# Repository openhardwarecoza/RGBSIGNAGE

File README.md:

# RGBSIGNAGE
Electronics and Firmware for an ESP8266 based RGB Sign

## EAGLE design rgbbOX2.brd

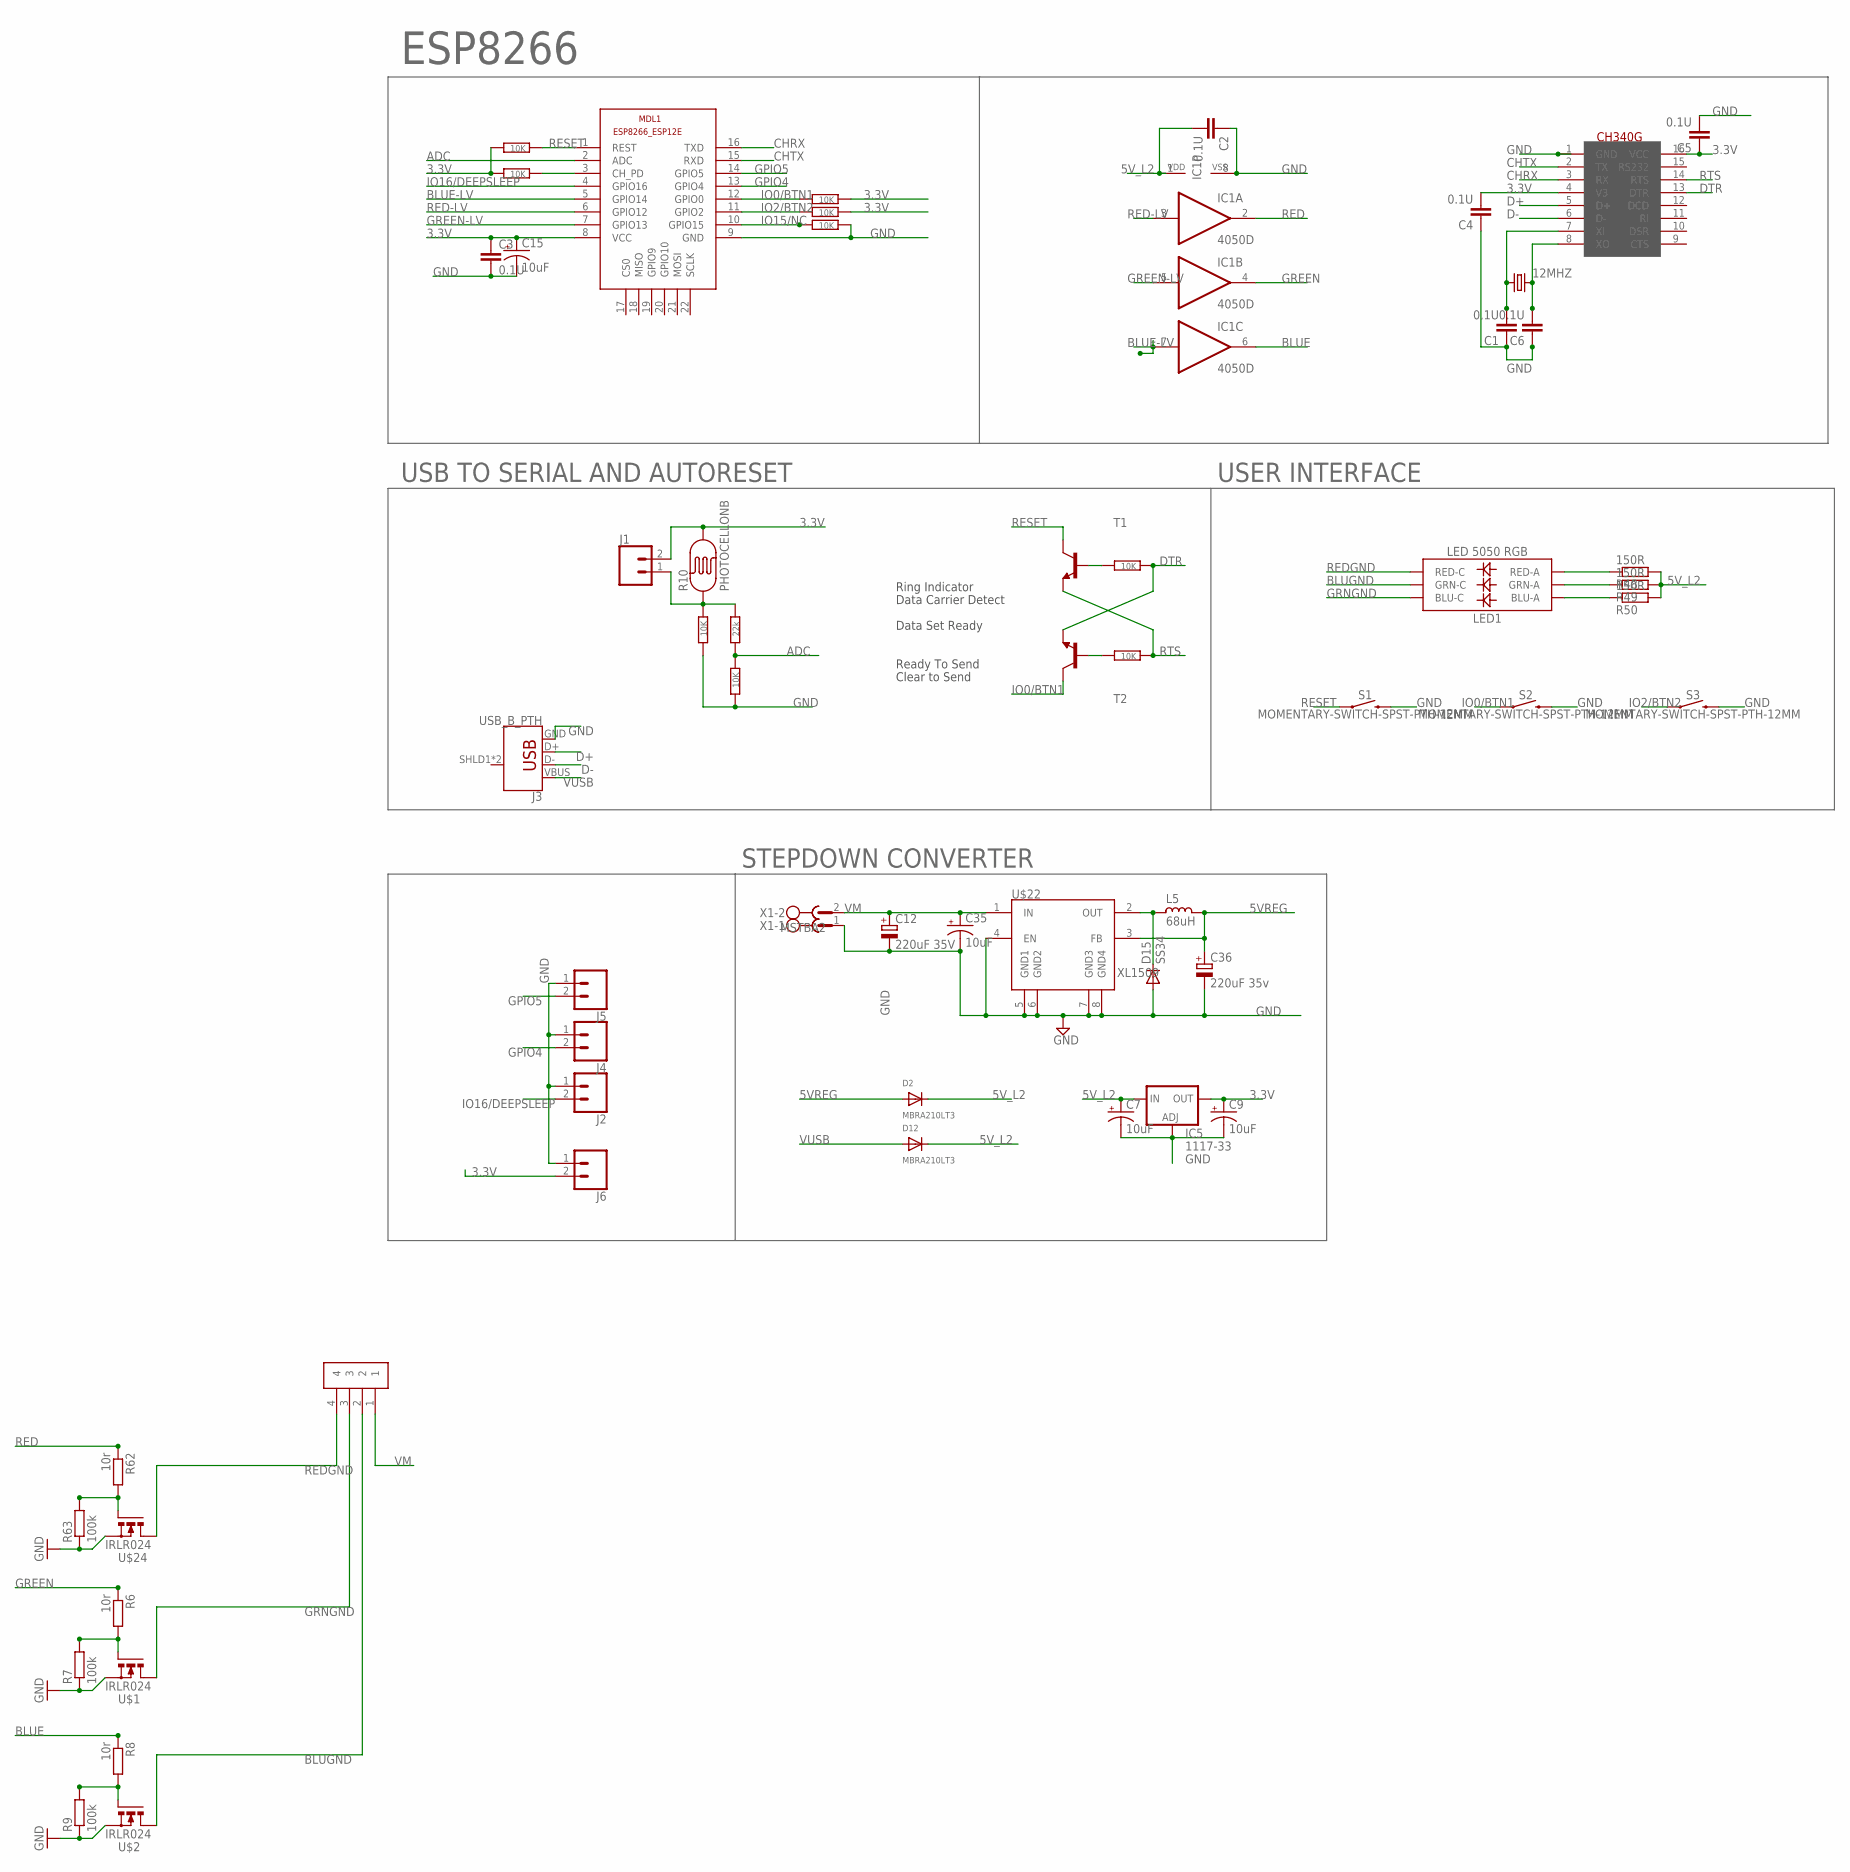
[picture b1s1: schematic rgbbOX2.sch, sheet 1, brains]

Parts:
12MHZ: CRYSTALHC49UP; HC49UP
C1, C2, C3, C4, C5, C6: 0.1U; C1206
C7, C9, C15, C35: 10uF; EIA3216
C12: 220uF 35V; E3,5-8
C36: 220uF 35v; E3,5-8
CON25: Phoenix Pluggable 3.81mm 4 way; 3.81MM-4WAY-PLUGGABLE-SCREW
D2, D12: MBRA210LT3; SMADIODE
D15: SS34; DO-214AC
IC1: 4050D; SO16
IC5: 1117-33; SOT223
J1, J2, J4, J5, J6: CONN_02LOCK; 1X02_LOCK
J3: USB_B_PTH; USB-B-PTH
L5: 68uH; CD75
LED1: LED 5050 RGB; LED-TRICOLOR-5050
MDL1: ESP8266-12EESP8266-ESP12E; ESP8266-ESP12E
R1, R2, R4, R5, R11, R12, R28, R29, R31: 10K; R1206
R3: 22k; R1206
R6, R8, R62: 10r; R1206
R7, R9, R63: 100k; R1206
R10: PHOTOCELLONB; ON_BOARD
R48, R49, R50: 150R; R1210
S1, S2, S3: MOMENTARY-SWITCH-SPST-PTH-12MM; TACTILE_SWITCH_PTH_12MM
T1, T2: MMBT2222ALT1-NPN-SOT23-BEC; SOT23-BEC
U$1, U$2, U$24: IRLR024; D-PAK_TO252AA
U$4: CH340G; SOIC16
U$22: XL1509; SO08
X1: MSTBA2

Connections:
3.3V: C3.1, C4.2, C5.1, C9.A (+), C15.A (+), IC5.4 (OUT), J1.2, J6.2, MDL1.8 (VCC), R10.2, R11.2, R12.2, R28.1, R29.1, U$4.4 (V3), U$4.16 (VCC)
5VREG: C36.+, D2.A, L5.1, U$22.3 (FB)
5V_L2: C2.2, C7.A (+), D2.C, D12.C, IC1.1 (VDD), IC5.3 (IN), R48.2, R49.2, R50.2
ADC: MDL1.2 (ADC), R3.1, R4.2
BLUE: IC1.6 (O), R8.1
BLUE-LV: IC1.7 (I), MDL1.5 (GPIO14)
BLUGND: CON25.2, LED1.6 (GRN-C), U$2.4 (D)
CHRX: MDL1.16 (TXD), U$4.3 (RX)
CHTX: MDL1.15 (RXD), U$4.2 (TX)
D+: J3.D+, U$4.5 (D+)
D-: J3.D-, U$4.6 (D-)
DTR: R1.2, T2.E, U$4.13 (DTR)
GND: C1.1, C2.1, C3.2, C4.1, C5.2, C6.1, C7.C (-), C9.C (-), C12.-, C15.C (-), C35.C (-), C36.-, D15.2 (A), IC1.8 (VSS), IC5.1 (ADJ), J2.1, J3.GND, J4.1, J5.1, J6.1, MDL1.9 (GND), R4.1, R5.1, R7.1, R9.1, R31.2, R63.1, S1.3 (2), S2.3 (2), S3.3 (2), U$1.3 (S), U$2.3 (S), U$4.1 (GND), U$22.4 (EN), U$22.5 (GND1), U$22.6 (GND2), U$22.7 (GND3), U$22.8 (GND4), U$24.3 (S), X1.1
GPIO4: J4.2, MDL1.13 (GPIO4)
GPIO5: J5.2, MDL1.14 (GPIO5)
GREEN: IC1.4 (O), R6.1
GREEN-LV: IC1.5 (I), MDL1.7 (GPIO13)
GRNGND: CON25.3, LED1.4 (BLU-C), U$1.4 (D)
IO0/BTN1: MDL1.12 (GPIO0), R12.1, S2.1, T2.C
IO2/BTN2: MDL1.11 (GPIO2), R11.1, S3.1
IO15/NC: MDL1.10 (GPIO15), R31.1
IO16/DEEPSLEEP: J2.2, MDL1.4 (GPIO16)
unnamed: R6.2, R7.2, U$1.1 (G)
unnamed: R62.2, R63.2, U$24.1 (G)
unnamed: D15.1 (C), L5.2, U$22.2 (OUT)
unnamed: 12MHZ.1, C1.2, U$4.7 (XI)
unnamed: 12MHZ.2, C6.2, U$4.8 (XO)
unnamed: R8.2, R9.2, U$2.1 (G)
unnamed: R1.1, T1.B
unnamed: R2.1, T2.B
unnamed: J1.1, R3.2, R5.2, R10.1
unnamed: MDL1.3 (CH_PD), R28.2
unnamed: LED1.3 (BLU-A), R50.1
unnamed: LED1.1 (GRN-A), R49.1
unnamed: LED1.2 (RED-A), R48.1
RED: IC1.2 (O), R62.1
RED-LV: IC1.3 (I), MDL1.6 (GPIO12)
REDGND: CON25.4, LED1.5 (RED-C), U$24.4 (D)
RESET: MDL1.1 (REST), R29.2, S1.1, T1.C
RTS: R2.2, T1.E, U$4.14 (RTS)
VM: C12.+, C35.A (+), CON25.1, U$22.1 (IN), X1.2
VUSB: D12.A, J3.VBUS

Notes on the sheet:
USB TO SERIAL AND AUTORESET
ESP8266
USER INTERFACE
Ring Indicator
Data Carrier Detect
Data Set Ready
Ready To Send
Clear to Send
STEPDOWN CONVERTER

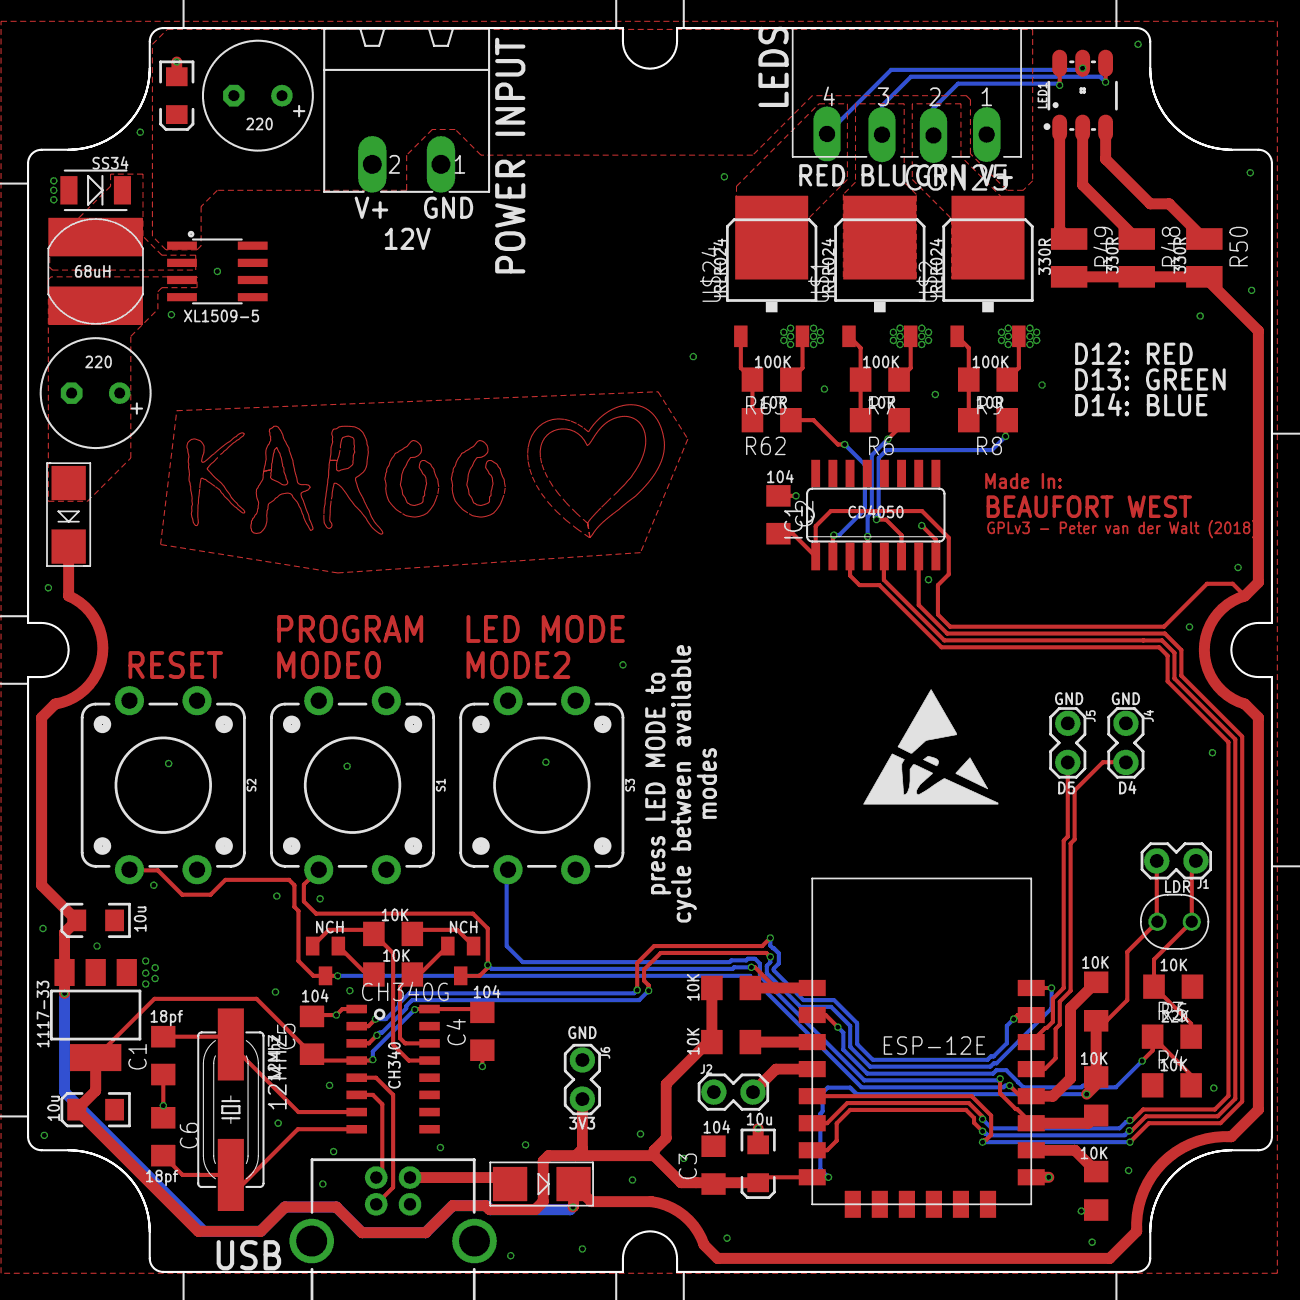
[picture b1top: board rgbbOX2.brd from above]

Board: 2 copper layers, 92.0 x 92.0 mm, 60 parts (0 on the bottom side), 42 nets.

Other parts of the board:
U$3: ESD_10.00

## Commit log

2018-10-23 Albie
2018-10-23 Working until you do a websocket call. Then the webserver stops responding. Need to switch to asyncwebserve
2018-10-23 Updated WebSocket
2018-10-24 Client working
2018-10-24 Start of ASYNC version
2018-10-24 Working Params, Spiffs, Scan and WebSocket Seq
2018-10-24 Captive Portal working
2018-10-24 Buttons and Wifi Select Sequence Working
2018-10-24 http params not working yet... commented out
2018-10-24 Post
2018-10-24 Post Dusk
2018-10-25 Dusk/Dawn Working
2018-10-25 c:reset

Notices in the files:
rgbbOX2.brd:
GPLv3 - Peter van der Walt (2018)
parts and their libraries:
SparkFun-Connectors: Licensing: Creative Commons ShareAlike 4.0 International - https://creativecommons.org/licenses/by-sa/4.0
rc-master-smd: Copyright (C) 2007, Bob Starr
